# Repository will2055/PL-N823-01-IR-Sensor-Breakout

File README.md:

# PL-N823-01-IR-Sensor-Breakout
PL-N823-01 Lensless IR Sensor breakout with signal amplifier and I2C ADC 

This board allows for digital sensor reading of IR signals from external sources. One such application can be the detection of heat given off by the human body. Operating voltage is 5V for the board as a whole, and while under 1mm thick materials detection can be as far away as 10cm to 20cm.

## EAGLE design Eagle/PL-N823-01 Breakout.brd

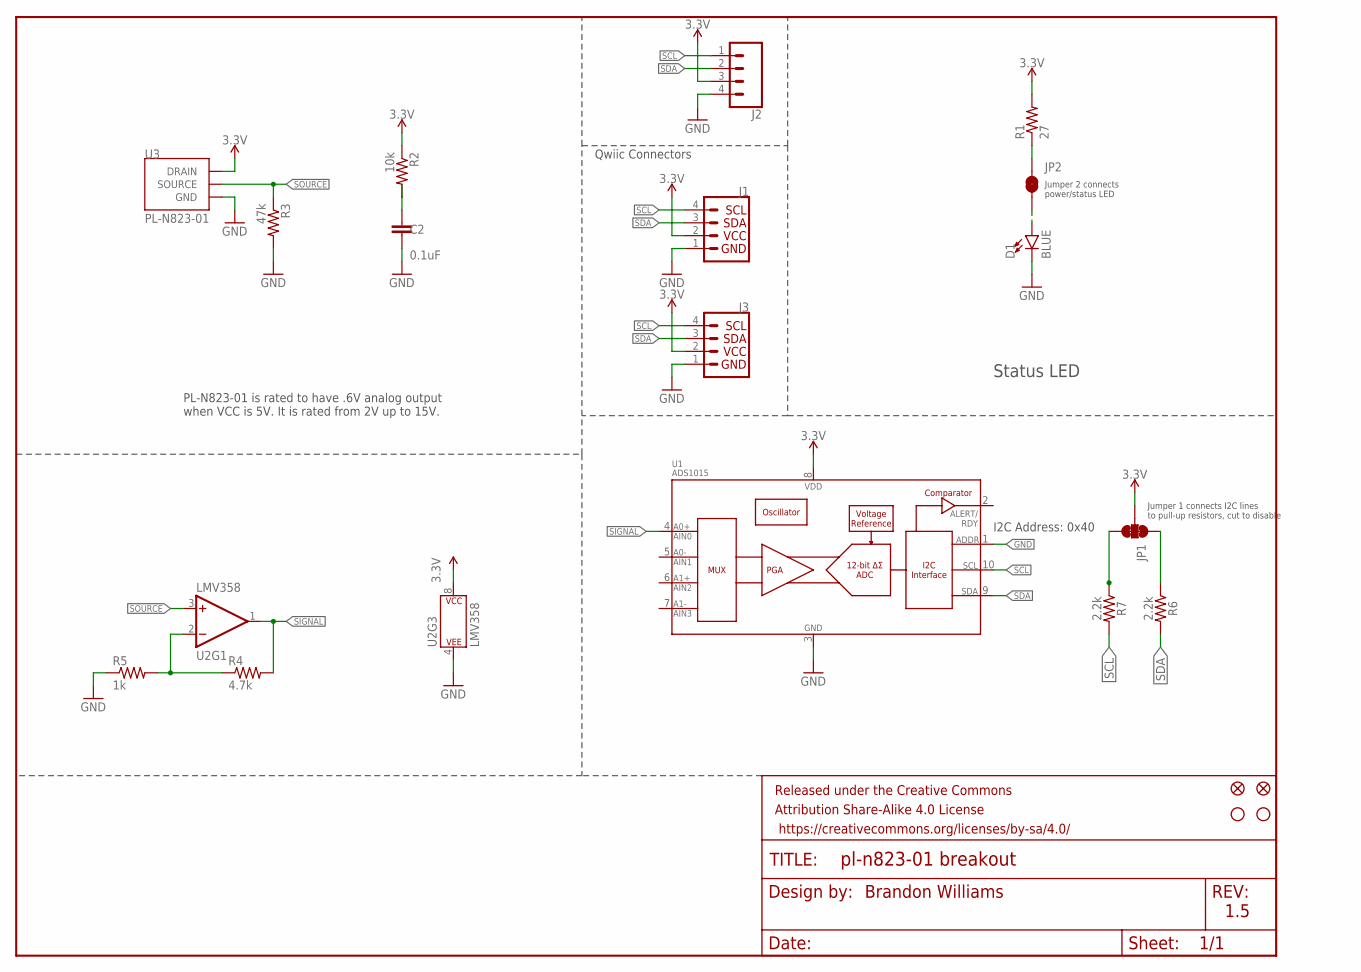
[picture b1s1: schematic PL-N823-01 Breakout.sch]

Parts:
C2: 0.1uF; 0603
D1: BLUE; LED-0603
FD1, FD2: FIDUCIALUFIDUCIAL; FIDUCIAL-MICRO
FRAME1: FRAME-LETTERNO_PACKAGE; DUMMY
H1, H2: STAND-OFFTIGHT; STAND-OFF-TIGHT
J1, J3: QWIIC_CONNECTORJS-1MM; 1X04_1MM_RA
J2: CONN_041X04_NO_SILK; 1X04_NO_SILK
JP1: JUMPER-SMT_3_2-NC_TRACE_SILK; SMT-JUMPER_3_2-NC_TRACE_SILK
JP2: JUMPER-SMT_2_NC_TRACE_SILK; SMT-JUMPER_2_NC_TRACE_SILK
R1: 27; 0603
R2: 10k; 0603
R3: 47k; 0603
R4: 4.7k; 0603
R5: 1k; 0603
R6, R7: 2.2k; 0603
U1: ADS1015; MSOP10
U2: LMV358; SO08
U3: PL-N823-01

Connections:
GND: C2.2, D1.C, J1.1 (GND), J2.4, J3.1 (GND), R3.2, R5.1, U1.1 (ADDR), U1.3 (VSS), U2.4 (P$V-), U3.GND@1 (GND), U3.GND@2 (GND)
unnamed: R4.1, R5.2, U2.2 (-IN)
unnamed: C2.1, R2.2
unnamed: JP2.1, R1.1
unnamed: JP1.3, R7.1
unnamed: JP1.1, R6.1
unnamed: D1.A, JP2.2
SCL: J1.4 (SCL), J2.1, J3.4 (SCL), R7.2, U1.10 (SCL)
SDA: J1.3 (SDA), J2.2, J3.3 (SDA), R6.2, U1.9 (SDA)
SIGNAL: R4.2, U1.4 (AIN0), U2.1 (OUT)
SOURCE: R3.1, U2.3 (+IN), U3.SOURCE
VCC: J1.2 (VCC), J2.3, J3.2 (VCC), JP1.2, R1.2, R2.1, U1.8 (VDD), U2.8 (P$V+), U3.DRAIN

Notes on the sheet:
Brandon Williams
1.5
I2C Address: 0x40
Status LED
Jumper 2 connects power/status LED
Jumper 1 connects I2C lines to pull-up resistors, cut to disable
PL-N823-01 is rated to have .6V analog output when VCC is 5V. It is rated from 2V up to 15V.
Qwiic Connectors

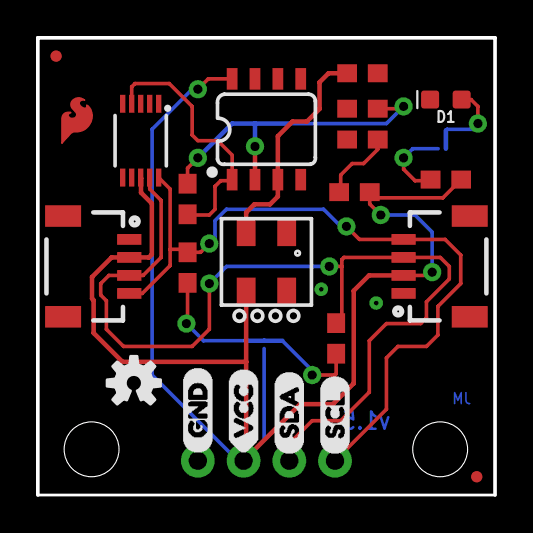
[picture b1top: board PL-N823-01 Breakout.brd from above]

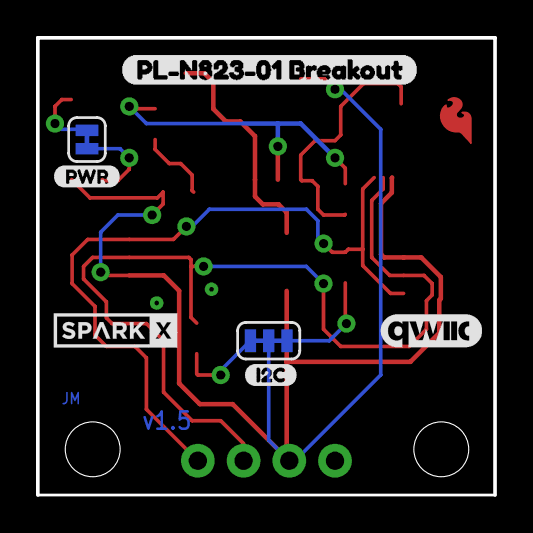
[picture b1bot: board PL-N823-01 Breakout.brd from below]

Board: 2 copper layers, 25.4 x 25.4 mm, 33 parts (7 on the bottom side), 12 nets.

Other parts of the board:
U$1: QWIIC_COPYRIGHT_SMALL
U$2: SFE_LOGO_FLAME_COPPER_EXPOSED_.1
U$3: GND0
U$4: SCL0
U$5: SDA0
U$6: VCC0
U$7: OSHW-LOGO-S
U$8: PL#N823#01_BREAKOUT0
U$9: PWR-()-03
U$10: SPARKX-SMALL
U$11: I2C0

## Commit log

2019-05-01 Uploaded Eagle Files
2019-05-01 Rename PL-N823-01 Analog Breakout.brd to Eagle/PL-N823-01 Analog Breakout.brd
2019-05-01 Rename PL-N823-01 Analog Breakout.pro to Eagle/PL-N823-01 Analog Breakout.pro
2019-05-01 Rename PL-N823-01 Analog Breakout.sch to Eagle/PL-N823-01 Analog Breakout.sch
2019-05-02 v1.5 file update
2019-05-02 upload datasheet and product description
2019-05-02 Rename PL-N823-01 Analog Breakout.brd to PL-N823-01 Breakout.brd
2019-05-02 Rename PL-N823-01 Analog Breakout.sch to PL-N823-01 Breakout.sch
2020-02-24 Updated PL-N823 Library

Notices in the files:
parts and their libraries:
SparkFun-Aesthetics: Licensing: Creative Commons ShareAlike 4.0 International - https://creativecommons.org/licenses/by-sa/4.0
SparkFun-Aesthetics: Released under the Creative Commons Attribution Share-Alike 4.0 License
SparkFun-Aesthetics: https://creativecommons.org/licenses/by-sa/4.0
